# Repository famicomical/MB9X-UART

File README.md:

# MB9X-UART
Allows you to program the Fujitsu F2MC-16LX series processors using an RS-232C serial port connection. It uses a 12-pin connector for direct connection to the JVC DT-V series monitors and an optional 10-pin connection as described in Fujitsu documentation. Note: [programming the DT-V monitors](dt-vmod) requires modifying the Signal PWB. 

The person assembling this board will need to procure their own USB to RS232-C cable and their own copy of the Fujitsu "FLASH MCU Programmer 16LX" software, which includes proprietary configuration files for the MCUs. I recommend installing [ISP-MB9X](https://isp-mb9x.sourceforge.net/) by Sergey Pinigin in addition to the [Fujitsu software](http://web.archive.org/web/20041020161858/http://www.fme.gsdc.de/products/utilitie.htm) to have some more fine control over programming operations.

## Example Usage
 - Identify the chip you are programming and set the DIP switches accordingly
   - Settings can be found in Fujitsu documentation. The /CS and RTS switches should stay ON.
 - Connect the USB-RS232C port to the assembled MB9X-UART PCB
    - extension of the USB cord is preferable to extending the RS232-C connection. in other words, connect the MB9X-UART directly to your adapter.
 - Connect the MB9X-UART to your target board, and turn on the power
 - Invoke the ISP-MB9X program from the command-line. 
   - For example: ```isp-mb9x.exe /1 /o4 /MB90F553A /b ROM /r```
uses serial port COM1 to dump the ROM from a Fujitsu MB90F553A running at 4MHz into a file called ROM. 
      - Caution: running the program without the /r command will erase the ROM from your MCU by default, so be careful!!
      - you must add the .mhx file extension manually as the isp-mb9x program will crash if you supply a file extension in the command line.
 - Wait for the read to complete being careful not to disturb the cables.
 - Power off your equipment and unplug the board

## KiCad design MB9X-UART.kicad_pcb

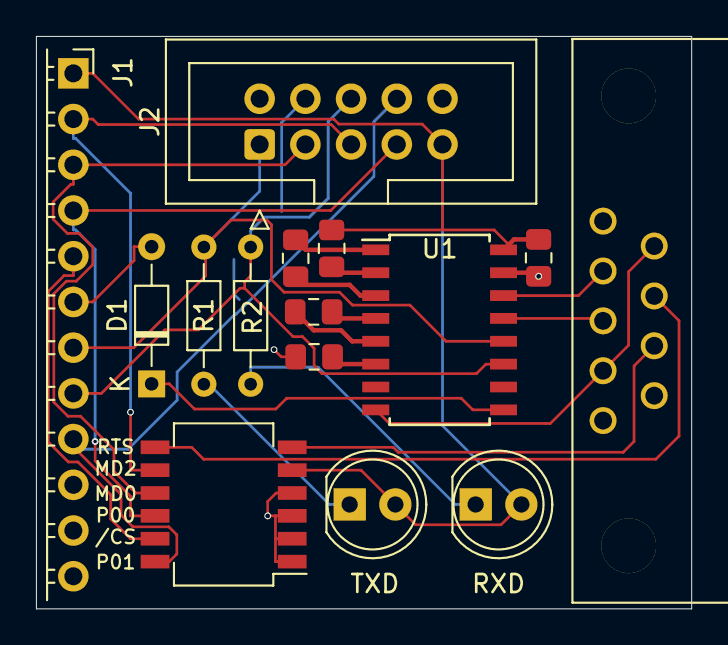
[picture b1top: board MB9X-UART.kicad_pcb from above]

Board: 2 copper layers, 36.4 x 31.8 mm, 15 parts (0 on the bottom side), 24 nets.

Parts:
C1, C2, C3, C4, C5: 1u; C_0805_2012Metric_Pad1.15x1.40mm_HandSolder
D1: BAT85; D_DO-34_SOD68_P7.62mm_Horizontal
J1: Conn_01x12_Female; PinSocket_1x12_P2.54mm_Horizontal
J2: Conn_02x05_Odd_Even; IDC-Header_2x05_P2.54mm_Vertical
J3: DB9_Female; A-DF 09 A&slash_KG-T2S
R1, R2: 1k; R_Axial_DIN0204_L3.6mm_D1.6mm_P7.62mm_Horizontal
RXD: R_LED; LED_D5.0mm
SW1: SW_DIP_x06; SW_DIP_SPSTx06_Slide_Copal_CHS-06B_W7.62mm_P1.27mm
TXD: Y_LED; LED_D5.0mm
U1: MAX232I; SOIC-16W_5.3x10.2mm_P1.27mm

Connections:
/!CS: J1.5, SW1.11
/CTS: J3.8, SW1.6
/MD0: J1.3, J2.3, SW1.9
/MD2: J1.2, J2.5, SW1.8
/P00: J1.4, J2.7, SW1.10
/P01: J1.9, J2.8, SW1.12
/RSTX: D1.2, J1.6
/RTS: J3.7, SW1.7
/SIN: J1.7, J2.1, R1.1, U1.12
/SOT: J1.8, J2.6, R2.1, U1.11
GND: C2.2, C5.2, J1.12, J2.4, J3.5, SW1.1, SW1.2, SW1.3, SW1.4, U1.15
unnamed: C1.1, U1.1
unnamed: C1.2, U1.3
unnamed: C2.1, U1.6
unnamed: C3.1, U1.4
unnamed: C3.2, U1.5
unnamed: C4.2, U1.2
unnamed: D1.1, U1.9
unnamed: R1.2, TXD.1
unnamed: R2.2, RXD.1
unnamed: J3.2, U1.14
unnamed: J3.3, U1.13
unnamed: J3.4, J3.6, U1.8
VCC: C4.1, C5.1, J1.1, J2.9, RXD.2, SW1.5, TXD.2, U1.16

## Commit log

2023-03-11 Update figure
2023-03-12 add mod guide
2023-03-12 update figures
2023-03-12 add figure
2023-03-12 add BOM
